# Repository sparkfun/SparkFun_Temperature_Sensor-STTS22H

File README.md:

# SparkFun Temperature Sensor STTS22H
========================================

<table class="table table-hover table-striped table-bordered">
    <tr>
        <th class="text-center"> 
        </th>
        <th class="text-center">
        </th>
    </tr>
    <tr align="center">
        <td></td>
        <td></td>
    </tr>
    <tr align="center">
        <td><a href="https://www.sparkfun.com/products/21262">SparkFun Temperature Sensor - STTS22H (Qwiic)</a></td>
        <td><a href="https://www.sparkfun.com/products/21273">SparkFun Micro Temperature Sensor - STTS22H (Qwiic)</a></td>
    </tr>
</table>

The [SparkFun Temperature Sensor - STTS22H (Qwiic)](https://www.sparkfun.com/products/21262) and the [SparkFun Micro Temperature Sensor - STTS22H (Qwiic)](https://www.sparkfun.com/products/21273) are Qwiic enabled breakout boards based on the ultralow-power, high-accuracy, digital temperature sensor STTS22H from ST Microelectronics. Thanks to its factory calibration the STTS22H offers high-end accuracy performance over the entire operating temperature range, reaching as low as ±0.5 °C without requiring any further calibration at the application level. 

Repository Contents
-------------------

* **/Documentation** - Data sheets, additional product information
* **/Hardware** - Eagle design files (.brd, .sch)
* **/Production** - Production panel files (.brd)

Documentation
--------------
* **[Library](https://github.com/sparkfun/SparkFun_STTS22H_Arduino_Library)** - Arduino library for the SparkFun Temperature Sensor STTS22H.
* **[Hookup Guide](https://learn.sparkfun.com/tutorials/sparkfun-temperature-sensor---stts22h-qwiic-hookup-guide)** - Basic hookup guide for the SparkFun Temperature Sensor STTS22H.

License Information
-------------------

This product is _**open source**_! 

Please review the LICENSE.md file for license information. 

If you have any questions or concerns on licensing, please contact technical support on our [SparkFun forums](https://forum.sparkfun.com/viewforum.php?f=152).

Distributed as-is; no warranty is given.

- Your friends at SparkFun.

_<COLLABORATION CREDIT>_

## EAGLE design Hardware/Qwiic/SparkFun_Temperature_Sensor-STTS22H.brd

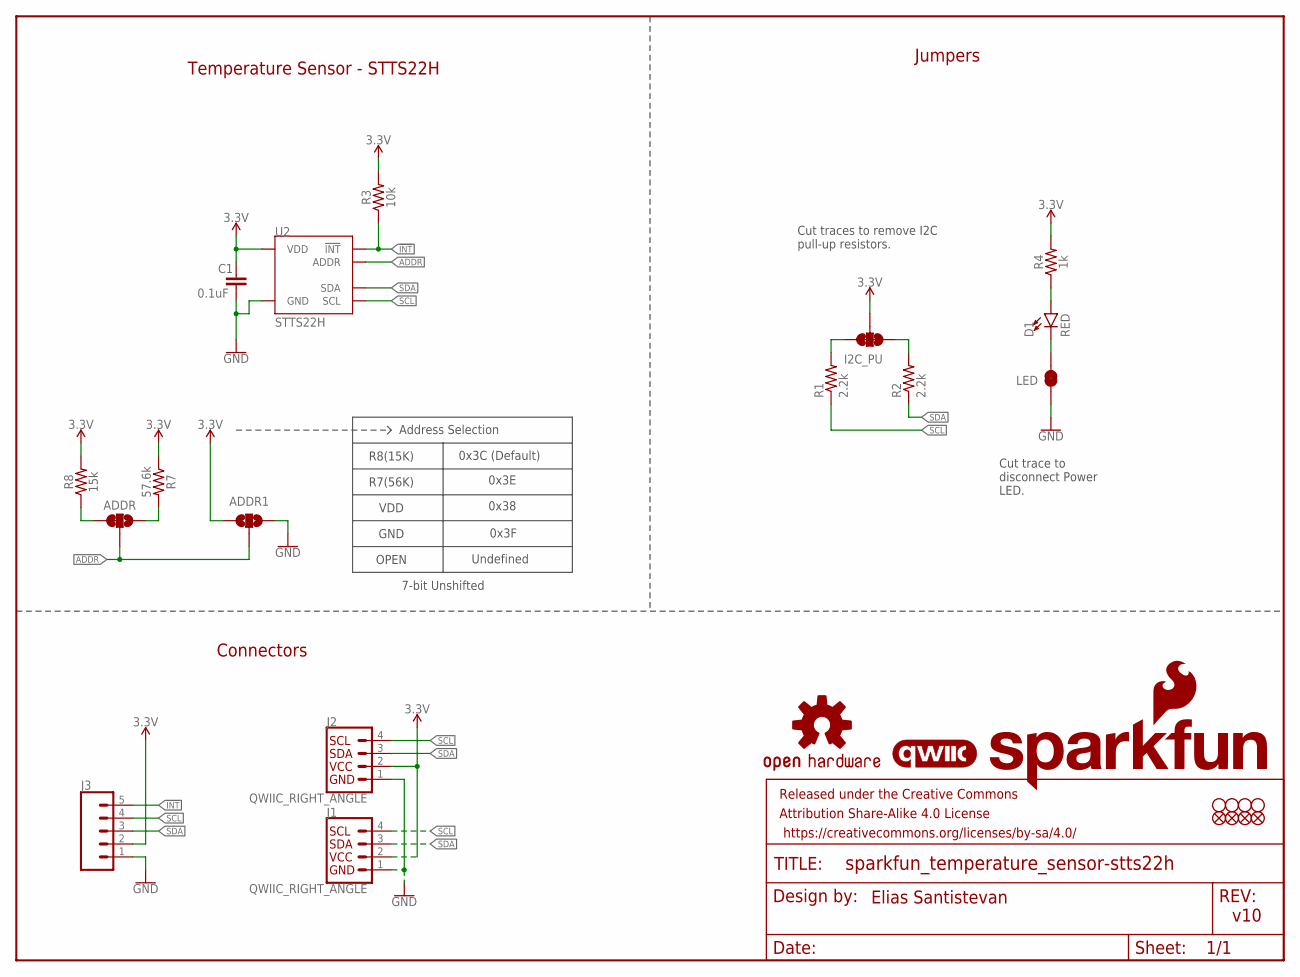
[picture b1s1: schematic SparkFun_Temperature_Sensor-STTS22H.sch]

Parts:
ADDR: JUMPER-SMT_3_1-NC_TRACE_SILK; SMT-JUMPER_3_1-NC_TRACE_SILK
ADDR1: JUMPER-SMT_3_NO_SILK; SMT-JUMPER_3_NO_SILK
C1: 0.1uF; 0603
D1: RED; LED-0603
FD1, FD2, FD3, FD4: FIDUCIAL1X2; FIDUCIAL-1X2
FRAME1: FRAME-LETTER; CREATIVE_COMMONS
I2C_PU: S_MODE; SMT-JUMPER_3_2-NC_TRACE_SILK
J1, J2: QWIIC_RIGHT_ANGLE; JST04_1MM_RA
J3: CONN_05NO_SILK; 1X05_NO_SILK
LED: JUMPER-SMT_2_NC_TRACE_SILK; SMT-JUMPER_2_NC_TRACE_SILK
LOGO2: OSHW-LOGOMINI; OSHW-LOGO-MINI
LOGO3: SFE_LOGO_NAME_FLAME.1_INCH; SFE_LOGO_NAME_FLAME_.1
LOGO4: QWIIC_LOGO_4MM; QWIIC_4MM
R1, R2: 2.2k; 0603
R3: 10k; 0603
R4: 1k; 0603
R7: 57.6k; 0603
R8: 15k; 0603
STANDOFF1, STANDOFF2, STANDOFF3, STANDOFF5: STAND-OFFTIGHT; STAND-OFF-TIGHT
U2: STTS22H; UDFN-6L

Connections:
3.3V: ADDR1.3, C1.1, I2C_PU.2, J1.2, J2.2, J3.2, R3.2, R4.2, R7.1, R8.2, U2.P3 (VDD)
!INT!: J3.5, R3.1, U2.P2 (!INT!)
ADDR: ADDR.2, ADDR1.2, U2.P4 (ADDR)
GND: ADDR1.1, C1.2, J1.1, J2.1, J3.1, LED.1, U2.P5 (GND), U2.P7 (GND)
unnamed: D1.A, R4.1
unnamed: D1.C, LED.2
unnamed: ADDR.3, R8.1
unnamed: I2C_PU.1, R1.2
unnamed: I2C_PU.3, R2.2
unnamed: ADDR.1, R7.2
SCL: J1.4, J2.4, J3.4, R1.1, U2.P1 (SCL)
SDA: J1.3, J2.3, J3.3, R2.1, U2.P6 (SDA)

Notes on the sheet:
Cut traces to remove I2C pull-up resistors.
v10
Jumpers
Cut trace to disconnect Power LED.
Connectors
Elias Santistevan
VDD
GND
OPEN
Undefined
7-bit Unshifted
R7(56K)
R8(15K)
0x38
0x3C (Default)
0x3E
0x3F
Temperature Sensor - STTS22H
Address Selection

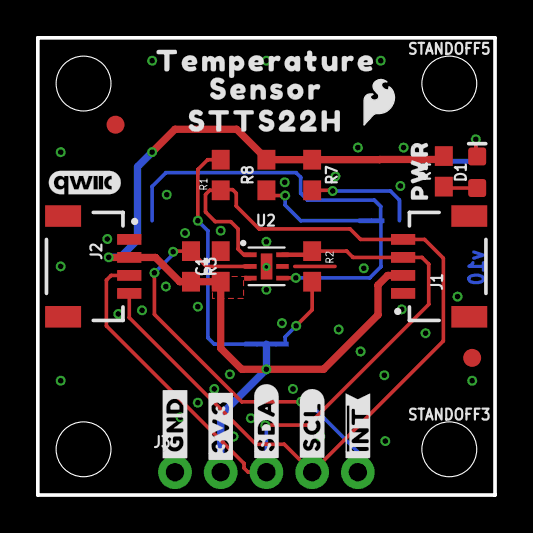
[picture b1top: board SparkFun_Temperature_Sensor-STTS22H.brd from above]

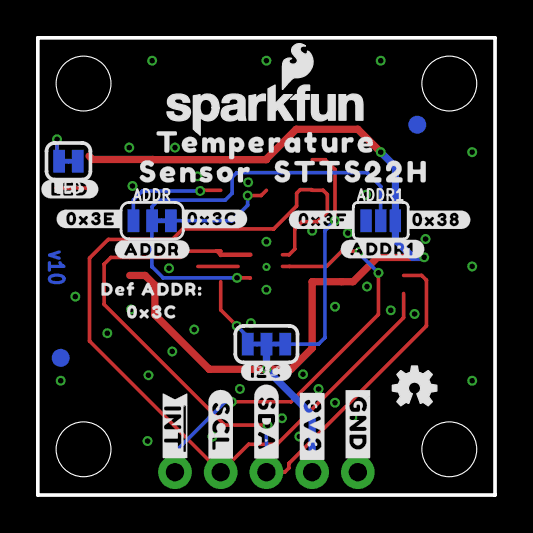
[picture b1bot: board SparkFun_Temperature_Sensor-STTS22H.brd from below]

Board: 2 copper layers, 25.4 x 25.4 mm, 56 parts (26 on the bottom side), 12 nets.

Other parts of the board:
U$1, U$9: #GND#3
U$2, U$10: #3V3#4
U$3: #SDA#5
U$4: #SCL#4
U$5: #SDA#7
U$6: #ADDR#6
U$7: #SCL#6
U$8: #ADDR1#9
U$11: ##INT##9
U$12: #0X3C#25
U$13: #0X3E#25
U$14: #0X3F#25
U$15: #0X38#25
U$16: #LED#11
U$17, U$23: TEMPERATURE23
U$18: ##INT##6
U$19, U$24: SENSOR24
U$20: SFE_LOGO_FLAME_.1
U$21: PWR9
U$22, U$26: STTS22H21
U$25: #I2C#11
U$27: DEF_ADDR#29
U$28: 0X3C30

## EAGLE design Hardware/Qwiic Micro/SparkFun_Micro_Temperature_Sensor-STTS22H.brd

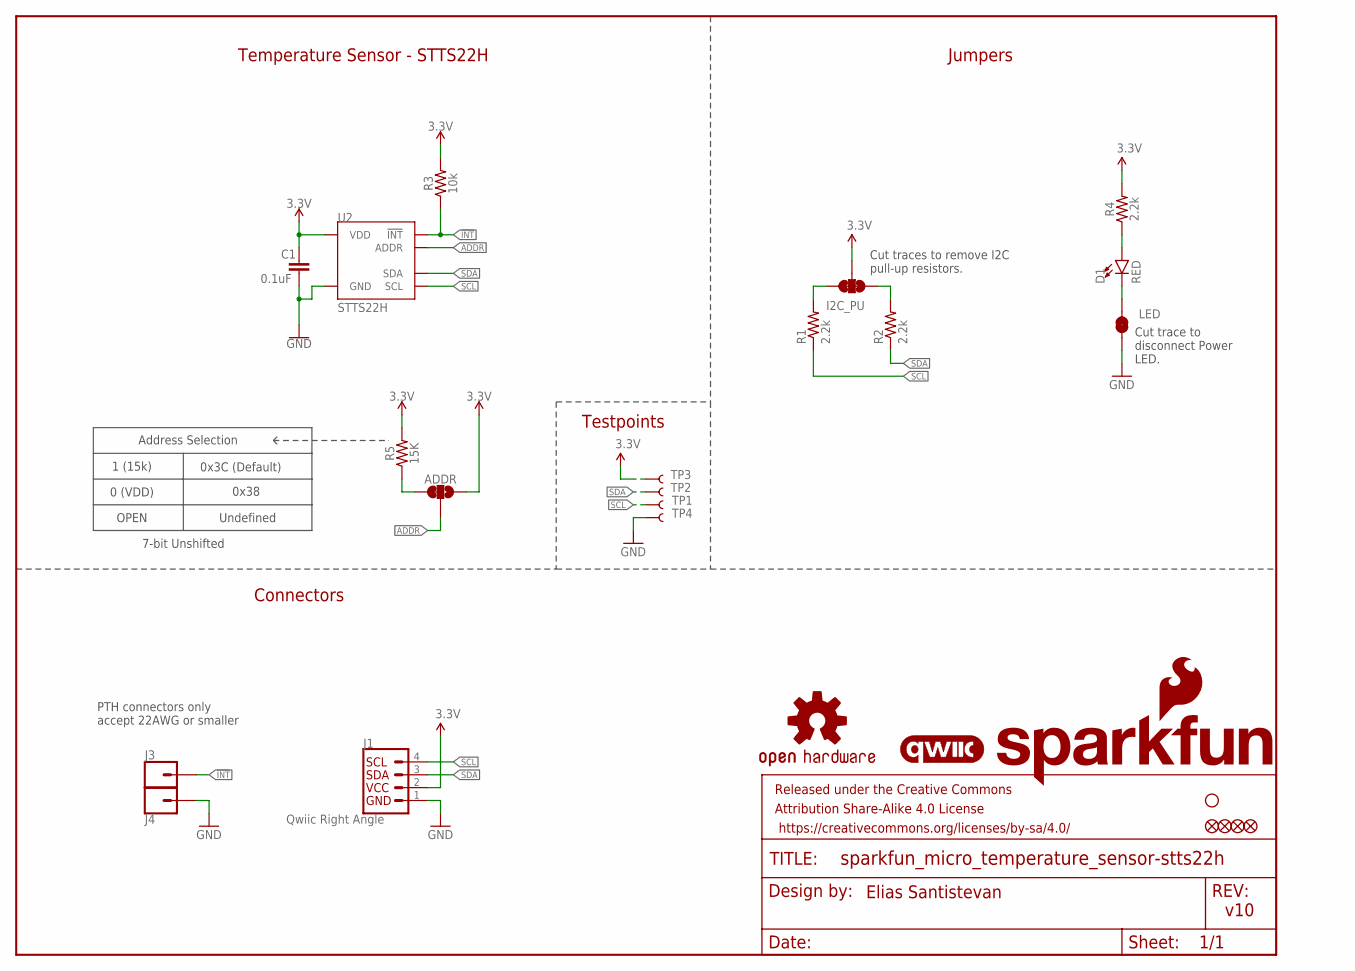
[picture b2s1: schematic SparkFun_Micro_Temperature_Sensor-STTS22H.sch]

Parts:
ADDR: JUMPER-SMT_3_1-NC_TRACE_SILK; SMT-JUMPER_3_1-NC_TRACE_SILK
C1: 0.1uF; 0402-TIGHT
D1: RED; LED-0402
FD1, FD2: FIDUCIALUFIDUCIAL; FIDUCIAL-MICRO
FID1, FID2: FIDUCIALUFIDUCIAL; FIDUCIAL-MICRO
FRAME1: FRAME-LETTER; CREATIVE_COMMONS
I2C_PU: S_MODE; SMT-JUMPER_3_2-NC_TRACE_SILK
J1: Qwiic Right Angle; JST04_1MM_RA
J3, J4: CONN_01_1MM; 1X01_1MM_NO_SILK
LED: JUMPER-SMT_2_NC_TRACE_SILK; SMT-JUMPER_2_NC_TRACE_SILK
LOGO1: QWIIC_LOGO_3MM; QWIIC_3MM
LOGO2: OSHW-LOGOMINI; OSHW-LOGO-MINI
LOGO3: SFE_LOGO_NAME_FLAMEBLANK; BLANK
R1, R2, R4: 2.2k; 0402-TIGHT
R3: 10k; 0402-TIGHT
R5: 15K; 0402-TIGHT
STANDOFF1: STAND-OFFTIGHT; STAND-OFF-TIGHT
TP1, TP2, TP3, TP4: TEST-POINT3; PAD.03X.03
U2: STTS22H; UDFN-6L

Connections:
3.3V: ADDR.1, C1.1, I2C_PU.2, J1.2, R3.2, R4.2, R5.2, TP3.1, U2.P3 (VDD)
!INT!: J3.1, R3.1, U2.P2 (!INT!)
ADDR: ADDR.2, U2.P4 (ADDR)
GND: C1.2, J1.1, J4.1, LED.1, TP4.1, U2.P5 (GND), U2.P7 (GND)
unnamed: ADDR.3, R5.1
unnamed: D1.A, R4.1
unnamed: D1.C, LED.2
unnamed: I2C_PU.1, R1.2
unnamed: I2C_PU.3, R2.2
SCL: J1.4, R1.1, TP1.1, U2.P1 (SCL)
SDA: J1.3, R2.1, TP2.1, U2.P6 (SDA)

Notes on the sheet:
Cut traces to remove I2C pull-up resistors.
v10
Jumpers
Cut trace to disconnect Power LED.
Connectors
Elias Santistevan
Testpoints
PTH connectors only accept 22AWG or smaller
1 (15k)
0 (VDD)
OPEN
Undefined
7-bit Unshifted
0x3C (Default)
0x38
Temperature Sensor - STTS22H
Address Selection

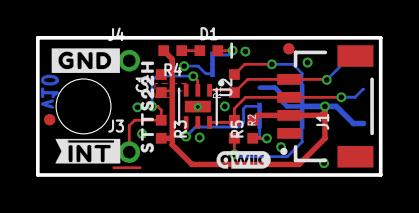
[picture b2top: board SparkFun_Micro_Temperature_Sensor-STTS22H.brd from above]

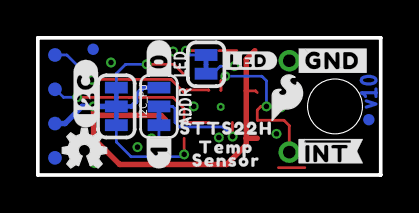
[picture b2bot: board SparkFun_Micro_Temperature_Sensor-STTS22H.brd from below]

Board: 2 copper layers, 19.1 x 7.6 mm, 40 parts (20 on the bottom side), 11 nets.

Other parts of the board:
U$1: #0#4
U$2: #1#4
U$3: #LED#2121
U$4, U$10: #GND#4
U$5, U$6: ##INT##9
U$7, U$8: STTS22H11
U$9: TEMP24
U$11: SENSOR25
U$12: #I2C#4
U$29: SFE_LOGO_FLAME_.1

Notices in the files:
parts and their libraries:
SparkFun-Aesthetics: Licensing: Creative Commons ShareAlike 4.0 International - https://creativecommons.org/licenses/by-sa/4.0
SparkFun-Aesthetics: Released under the Creative Commons Attribution Share-Alike 4.0 License
SparkFun-Aesthetics: https://creativecommons.org/licenses/by-sa/4.0
